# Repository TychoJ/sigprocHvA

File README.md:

# sigprocHvA
## Ned
Voor een opdracht van de HvA moet een filter ontworpen worden. Dit is voor het tweedejaars vak signaalverwerking toepassing. Dit filter moet zowel analoog als digitaal ontworpen worden en hier moet een verslag voor worden geschreven in het Nederlands.
___
## ENG
For a lab from the Amsterdam University of Applied there needed be a filter designed. This filter needed to be implemented analog as wel as digitally. Afterwords a report has to be written in dutch for this lab.
___

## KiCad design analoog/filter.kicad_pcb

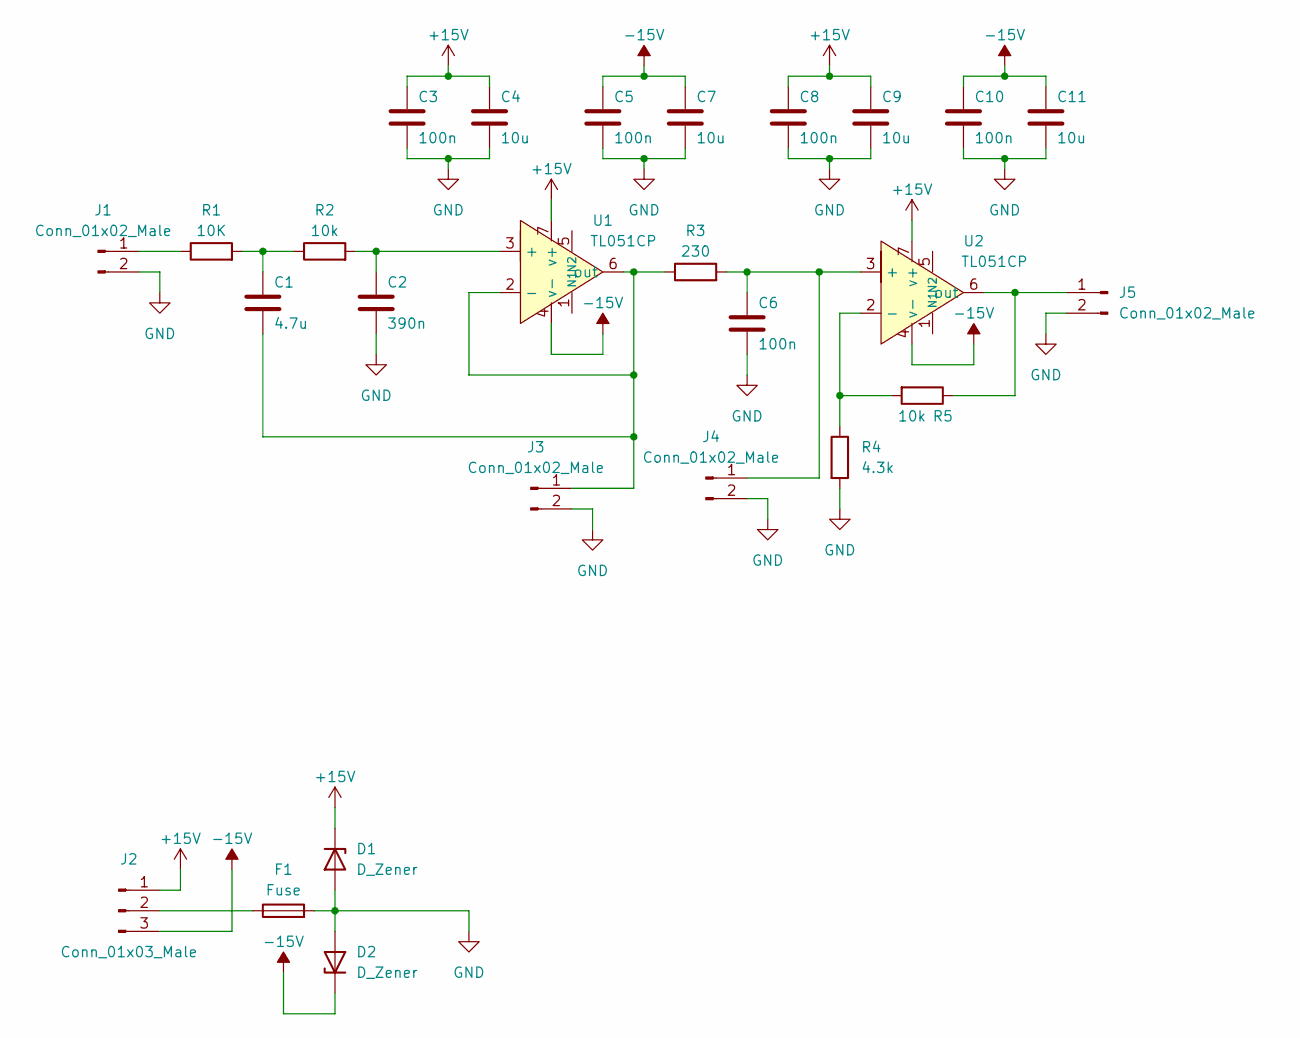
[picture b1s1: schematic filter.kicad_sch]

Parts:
C1: 4.7u; C_0805_2012Metric_Pad1.18x1.45mm_HandSolder
C2: 390n; C_0805_2012Metric_Pad1.18x1.45mm_HandSolder
C3, C5, C6, C8, C10: 100n; C_0805_2012Metric_Pad1.18x1.45mm_HandSolder
C4, C7, C9, C11: 10u; C_1206_3216Metric_Pad1.33x1.80mm_HandSolder
D1, D2: D_Zener; D_SOD-323_HandSoldering
F1: Fuse; Fuse_0805_2012Metric_Pad1.15x1.40mm_HandSolder
J1, J3, J4, J5: Conn_01x02_Male; PinSocket_1x02_P2.54mm_Vertical
J2: Conn_01x03_Male; PinSocket_1x03_P2.54mm_Vertical
R1: 10K; R_0805_2012Metric_Pad1.20x1.40mm_HandSolder
R2, R5: 10k; R_0805_2012Metric_Pad1.20x1.40mm_HandSolder
R3: 230; R_0805_2012Metric_Pad1.20x1.40mm_HandSolder
R4: 4.3k; R_0805_2012Metric_Pad1.20x1.40mm_HandSolder
U1, U2: TL051CP; DIP-8_W7.62mm_Socket_LongPads

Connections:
+15V: C3.1, C4.1, C8.1, C9.1, D1.1 (K), J2.1, U1.7 (v+), U2.7 (v+)
-15V: C5.1, C7.1, C10.1, C11.1, D2.1 (K), J2.3, U1.4 (v-), U2.4 (v-)
GND: C2.2, C3.2, C4.2, C5.2, C6.2, C7.2, C8.2, C9.2, C10.2, C11.2, D1.2 (A), D2.2 (A), F1.2, J1.2, J3.2, J4.2, J5.2, R4.2
unnamed: C1.1, R1.2, R2.1
unnamed: C1.2, J3.1, R3.1, U1.2 (-), U1.6 (out)
unnamed: C2.1, R2.2, U1.3 (+)
unnamed: C6.1, J4.1, R3.2, U2.3 (+)
unnamed: F1.1, J2.2
unnamed: J1.1, R1.1
unnamed: J5.1, R5.1, U2.6 (out)
unnamed: R4.1, R5.2, U2.2 (-)

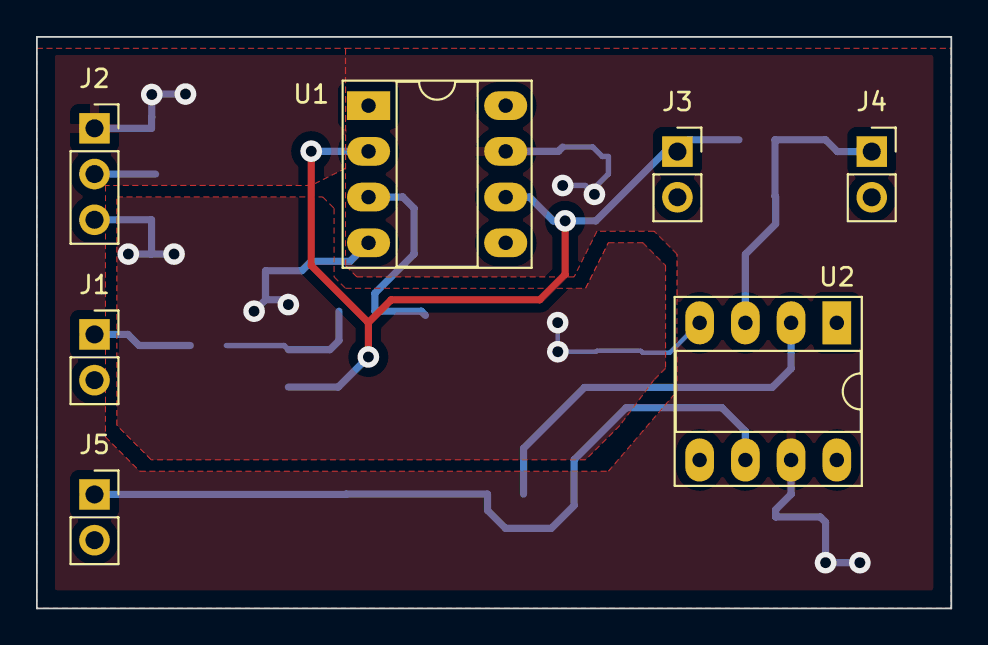
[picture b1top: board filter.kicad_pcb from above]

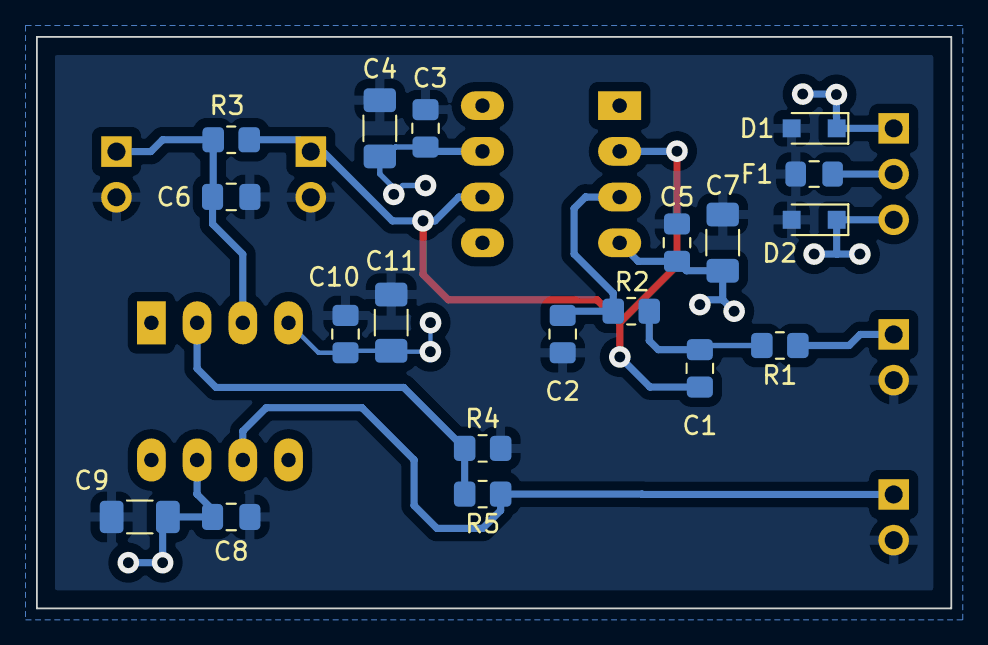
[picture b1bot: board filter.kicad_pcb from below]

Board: 2 copper layers, 50.8 x 31.8 mm, 26 parts (19 on the bottom side), 11 nets.

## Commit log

2022-01-17 changed file structure
2022-01-17 added intial latex files
2022-01-18 added LTspice files
2022-02-06 Filter code gemaakt en gecompileert. Nog niet getest.
2022-02-06 start of analog report
2022-02-06 sample rate fix
2022-02-06 alles + bullshit
2022-02-06 zucht en steun
2022-02-06 update gitignore for AS
2022-02-06 fuck it neem
2022-02-06 v1 of H1.4
2022-02-06 fixed allignment
2022-02-06 nieuwe branch tijd
2022-02-06 alsjeblieft tiego
2022-02-06 analoog V1 af
2022-02-06 zucht
2022-02-08 test dit pls
2022-02-08 ; fix
2022-02-08 ISNAN en adc2dac
2022-02-08 floats
2022-02-08 poesen
2022-02-08 delen door 1024
2022-02-08 added H2.1 2.2 and 2.3
